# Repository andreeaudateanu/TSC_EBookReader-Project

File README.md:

# Proiect TSC - E-Book Reader
## Udățeanu Andreea-Laura

Acest proiect reprezinta un sistem embedded de tip **E-Book Reader**, bazat pe microcontrollerul **ESP32-C6**. Dispozitivul este capabil sa afiseze continut text pe un ecran **E-Paper**, oferind o solutie cu consum redus de energie, ideala pentru citirea offline a documentelor. Sistemul include, de asemenea, functionalitati precum citire de pe card SD, afisare dinamica, butoane pentru control si conectivitate extinsa prin interfata I2C.

# Diagrama bloc

# Functionalitati Hardware

Proiectul utilizeaza microcontrollerul **ESP32-C6-WROOM-1-N8**, un modul avansat cu suport pentru **Wi-Fi 6**, **Bluetooth Low Energy 5.0** si arhitectura **RISC-V**:

## Microcontrollerul ESP32-C6

- Modul avansat cu suport pentru **Wi-Fi 6**, **Bluetooth Low Energy 5.0** si arhitectura **RISC-V**
- **Interfete:** SPI, I2C, UART, USB, PWM, GPIO
	- **SPI (Serial Peripheral Interface):** este utilizat pentru comunicatia rapida cu dispozitive precum E-Paper Display-ul, memoria NOR Flash si cardul microSD.
	- **I2C (Inter-Integrated Circuit):** este o magistrala seriala bidirectionala cu doi pini (SDA si SCL), folosita pentru conectarea senzorului BME688, RTC-ului DS3231SN si monitorului de baterie MAX17048.
	- **UART (Universal Asynchronous Receiver/Transmitter):** interfata seriala folosita pentru comunicatie cu terminalul serial (TX/RX).
	- **GPIO (General Purpose Input/Output):** pini de uz general configurati ca intrare/iesire digitala – utilizati pentru butoane, controlul ecranului E-Ink, etc.

- **Caracteristici speciale:** ofera suport pentru moduri de economisire (deep sleep)
- **Conexiuni:** Interfata centrala – conecteaza toate modulele externe din cadrul proiectului(E-Paper, SD card, senzori, RTC, memorie NOR Flash, etc.)

## Alimentare si protectie

### MAX17048 – Monitorizare nivel de baterie Li-Po
- **Comunicare:** prin interfata I2C cu ESP32-C6 (SCL, SDA)
- **Iesire:** are la iesire un semnal ALERT pentru nivel critic baterie

### MCP73831 – Controller de incarcare a bateriei Li-Po
- **Incarcare:** utilizeaza o celula Li-Po prin USB (VBUS) → 4.2V
- **Curent de incarcare:** pana la 500 mA
- **LED-uri:** care indica starea de incarcare (CHG_LED)

### XC6220A331MR-G – Regulator de tensiune LDO
- Primeste la intrare 5V prin USB (VBUS), iar la iesire transmite o tensiune de 3.3V
- **Curent maxim:** 200 mA
- **Consum standby:** <1 µA

### Conector USB-C si Protectie ESD
- **Conector USB-C:** utilizat atat pentru alimentarea dispozitivului (VBUS) cat si pentru comunicatie USB cu microcontrollerul ESP32-C6.

- **Protectie ESD:** implementata pe liniile de date si alimentare folosind diode TVS dedicate:
USBLC6-2SC6Y – protejeaza liniile D+ si D−. PMF0501 – asigura protectie suplimentara pe linia de alimentare VBUS.
- **Utilizare:** permite incarcarea bateriei prin controllerul MCP73831, dar si programarea/diagnosticarea ESP32-C6 fara conexiuni suplimentare.

## Stocare

### SD Card
- **Functie:** citire/scriere a fisierelor E-Book din cardul microSD
- **Interfata:** SPI partajata cu E-Paper
- **Semnale:** SS_SD, MOSI, MISO, SCK
- **Slot:** 112A-TAAR-R03

### W25Q512JVEIQ – Memorie NOR Flash externa 64MB
- **Capacitate:** 64 MB
- **Interfata:** conectata la magistrala SPI (nu partajeaza cu E-Paper)
- **Semnale:** FLASH_CS, MOSI, MISO, SCK
- **Functie:** stocare fonturi, imagini, firmware, configurari

## Afisaj E-Paper

- Interfete SPI si GPIO dedicate, avand semnale precum: CS (EPD_CS), DC (EPD_DC), RST (EPD_RST), BUSY (EPD_BUSY), MOSI, SCK  
## **Header special EPD** cu 20 pini
## **Controlul alimentarii EPD:** 
Permite microcontrollerului sa activeze sau sa dezactiveze alimentarea modulului E-Paper pentru a economisi energie, avand la iesire o tensiune de 3V3
## **Selectare mod:** 
Comutator tip jumper pentru a selecta tipul de display (circuit EPD driver dedicat)
- Consum 0 in standby, ideal pentru afisaj static

## Senzor de Mediu BME688
- **Functionalitati:** temperatura, umiditate, presiune, calitate aer (VOC)
- **Interfata:** I2C
- **Pini:** SDA, SCL legati la magistrala I2C comuna
- **Tensiune de alimentare:** 3.3V

## Modul RTC – DS3231SN
- **Functie:** surprinde timpul real cu precizie ±2ppm, avand suport deep sleep
- **Conexiune:** I2C – partajeaza pinii SDA/SCL cu senzorul BME688 si cu monitorizatorul de baterie MAX17048
- **Iesiri:** semnal 32kHz si semnal de intrerupere (INT_RTC)
- **Alimentare:** 3.3V, avand si backup intern (capacitor)

## Functii de control, reset si protectie

### Butoane de Control
- **BOOT / RESET si IO/CHANGE personalizat:** conectate pe GPIO cu retele RC
- **Functii:** BOOT: initializare microcontroller in modul bootloader, RESET: resetare generala a sistemului si IO/CHANGE: buton suplimentare pentru interactiuni custom de tipul schimbarii paginii, a meniului, etc.

### BD5229G-TR – Voltage Supervisor
- **Rol:** detecteaza scaderile de tensiune (brown-out) sub un anumit prag critic si genereaza automat un semnal de rest
- **Asigura o pornirea sigura a sistemului

### Protectii ESD si Interfete Extensibile

- **Linii protejate:** toate magistralele sensibile – USB, SPI, I2C si GPIO – sunt protejate impotriva descarcarilor electrostatice (ESD) prin diode (ex: **USBLC6-2SC6Y**, **PGB1010603MR**, **MBR0530**).
- **Conector Qwiic / Stemma QT:** ofera o interfata I2C standard (3.3V, GND, SDA, SCL) pentru extinderea rapida a sistemului cu senzori si periferice de la SparkFun sau Adafruit, fara necesitatea lipirii.
- **Paduri de test:** sunt incluse pe PCB pentru depanare usoara, verificari de semnal si programare.

### Consum de energie estimativ

| Componenta                | Consum aproximativ   |
|:--------------------------|:---------------------|
| ESP32-C6                  | 120–150 mA           |
| E-Paper Display           | 20–40 mA             |
| Senzor BME688             | 1–2 mA               |
| RTC DS3231SN              | 200 µA               |
| SD Card                   | 40–100 mA            |
| MAX17048                  | 50 µA                |
| NOR Flash (W25Q512JVEIQ)  | 20 mA                |
| Total sistem - mod activ  | aprob. 300 mA        |
| Total sistem - deep sleep | max. 10 µA           |

Daca nu sunt dezactivate toate modulele fizic (cu MOSFET sau power gate), deep sleep-ul poate ajunge usor la 1–2 mA, deci <10 µA este ideal si atins doar cu management riguros al energiei.

### Alocarea pinilor

## E-Paper Display

| Pin ESP32-C6 | Functie     | Utilizare                               |
|--------------|-------------|------------------------------------------|
| IO3  (26)    | EPD_BUSY    | Semnalizează dacă ecranul este activ    |
| IO5  (5)     | EPD_DC      | Schimba modul intre date și comanda     |
| IO6  (6)     | SCK         | Linie de ceas SPI - transfer de date    |
| IO7  (7)     | MOSI        | Trimitere date către ecran prin SPI     |
| IO10 (11)    | EPD_CS      | Activare comunicație cu modulul EPD     |
| IO23 (21)    | EPD_RST     | Resetare ecran                          |
| IO20 (18)    | EPD_3V3_C   | Control tensiune de alimentare 3V3 EPD  |

## Magistrala I2C (MAX17048, RTC DS3231, BME688)

| Pin ESP32-C6 | Functie     | Utilizare                               |
|--------------|-------------|------------------------------------------|
| IO21 (19)    | SDA         | Linie de transmitere date I2C           |
| IO22 (20)    | SCL         | Linie de ceas I2C                       |
| IO19 (17)    | I2C_PW      | Pornire/oprire senzori I2C              |

## Modul RTC DS3231SN

| Pin ESP32-C6 | Functie     | Utilizare                               |
|--------------|-------------|------------------------------------------|
| IO0 (8)      | INT_RTC     | Semnal de întrerupere RTC               |
| IO1 (9)      | 32KHz       | Iesire ceas precis                      |
| IO18 (16)    | RTC_RST     | Resetare hardware al modulului RTC      |

## USB
| Pin ESP32-C6 | Functie     | Utilizare                               |
|--------------|-------------|------------------------------------------|
| IO12 (13)    | USB_D-      | Linia negativa de comunicatie USB       |
| IO13 (14)    | USB_D+      | Linia pozitiva de comunicatie USB       |

## Seriala UART

| Pin ESP32-C6 | Functie     | Utilizare                               |
|--------------|-------------|------------------------------------------|
| IO16 (25)    | TX          | Transmisie UART                         |
| IO17 (24)    | RX          | Receptie UART                           |

## SD Card

| Pin ESP32-C6 | Functie     | Utilizare                               |
|--------------|-------------|------------------------------------------|
| IO2 (27)     | MISO        | Receptie date                           |
| IO4 (4)      | SS_SD       | Selectare modul SD                      |
| IO6 (6)      | SCK         | Ceas SPI                                |
| IO7 (7)      | MOSI        | Transmisie date                         |

## Memorie Externa NOR Flash 64MB

| Pin ESP32-C6 | Functie     | Utilizare                               |
|--------------|-------------|------------------------------------------|
| IO11 (12)    | FLASH_CS    | Selectare chip NOR                      |
| IO2  (27)    | MISO        | Receptie date                           |
| IO6  (6)     | SCK         | Ceas SPI                                |
| IO7  (7)     | MOSI        | Transmisie date                         |

## Butoane

| Pin ESP32-C6 | Functie     | Utilizare                               |
|--------------|-------------|------------------------------------------|
| EN   (3)     | RESET       | Resetare microcontroller                |
| IO8  (10)    | IO/BOOT     | Buton BOOT (în modul de programare)     |
| IO15 (23)    | IO/CHANGE   | Buton custom pentru diverse actiuni     |

## Alimentare si Masă

| Pin ESP32-C6 | Functie     | Utilizare                               |
|--------------|-------------|------------------------------------------|
| Pin 2        | 3V3         | Alimentare principala la 3.3V           |
| Pin 1        | GND         | Conectare la masa                       |

## Bill of Materials

| Componenta | Link Cumpărare | Datasheet |
|------------|-----------------|-----------|
| Condensatoare Tantalum | [Buy](https://ro.mouser.com/ProductDetail/KYOCERA-AVX/TAJW107M010RNJ?qs=Wtp%252Bf%2FAeVqIH8v1VxV%252B1Rg%3D%3D) | [Datasheet](https://ro.mouser.com/datasheet/2/40/TAJ-3165264.pdf) |
| Rezistente R0402 | [Buy](https://store.comet.srl.ro/Search/?keywords=r0402#eyJpcHAiOiIyMCIsIm0iOiIiLCJrIjoicjA0MDIifQ%3D%3D) | [Datasheet](https://www.yageo.com/upload/media/product/products/datasheet/rchip/PYu-RC_Group_51_RoHS_L_12.pdf) |
| Condensatoare C0402 | [Buy](https://store.comet.srl.ro/CatalogueFarnell/Search/?keywords=c0402#eyJpcHAiOiIyMCIsImsiOiJjMDQwMiJ9) | [Datasheet](https://componentsearchengine.com/Datasheets/2/CC0402MRX5R5BB106.pdf) |
| 112A-TAAR-R03 | [Buy](https://store.comet.srl.ro/Catalogue/Product/43497/) | [Datasheet](https://www.snapeda.com/parts/112A-TAAR-R03/Attend/datasheet/) |
| SD0805S020S1R0 | [Buy](https://ro.mouser.com/ProductDetail/KYOCERA-AVX/SD0805S020S1R0?qs=jCA%252BPfw4LHbpkAoSnwrdjw%3D%3D) | [Datasheet](https://ro.mouser.com/datasheet/2/40/schottky-3165252.pdf) |
| MBR0530 | [Buy](https://ro.mouser.com/ProductDetail/onsemi-Fairchild/MBR0530?qs=VOMQJJE%252BBNniwJKcE3T43Q==) | [Datasheet](https://ro.mouser.com/datasheet/2/308/MBR0530_D-1810985.pdf) |
| CHG_LED | [Buy](https://ro.mouser.com/ProductDetail/Kingbright/KP-1608SURCK?qs=2JU0tDl2GZ3FuyEWfBV1%2Fg==) | [Datasheet](https://www.snapeda.com/parts/KP-1608SURCK/Kingbright/datasheet/) |
| USBLC6-2SC6Y | [Buy](https://ro.mouser.com/ProductDetail/STMicroelectronics/USBLC6-2SC6Y?qs=gNDSiZmRJS%2FOgDexvXkdow%3D%3D) | [Datasheet](https://ro.mouser.com/datasheet/2/389/usblc6_2sc6y-1852505.pdf) 
| PGB1010603MR | [Buy](https://www.digikey.com/en/products/detail/littelfuse-inc/PGB1010603MR/715755) | [Datasheet](https://www.littelfuse.com/assetdocs/pulseguard-esd-suppressors-pgb1-datasheet?assetguid=8a337998-d54d-466b-be4e-dc5bcd1f9321) |
| ESP32-C6-WROOM-1-N8 | [Buy](https://ro.mouser.com/ProductDetail/Espressif-Systems/ESP32-C6-WROOM-1-N8?qs=8Wlm6%252BaMh8ST02Gmwp74cw%3D%3D) | [Datasheet](https://ro.mouser.com/datasheet/2/891/Espressif_ESP32_C6_WROOM_1__Datasheet_V0_1_PRELIMI-3239987.pdf) |
| DS3231SN | [Buy](https://store.comet.srl.ro/Catalogue/Product/47690/) | [Datasheet](https://ro.mouser.com/datasheet/2/609/DS3231-3421123.pdf) |
| BME680 | [Buy](https://ro.mouser.com/ProductDetail/Bosch-Sensortec/BME688?qs=IS%252B4QmGtzzqQoVDscqwx3A%3D%3D) | [Datasheet](https://ro.mouser.com/datasheet/2/783/bst_bme688_fl000-2307034.pdf) |
| MAX17048 | [Buy](https://ro.mouser.com/ProductDetail/Analog-Devices-Maxim-Integrated/MAX17048G%2bT10?qs=D7PJwyCwLAoGnnn8jEPRBQ%3D%3D) | [Datasheet](https://ro.mouser.com/datasheet/2/609/MAX17048_MAX17049-3469099.pdf) |
| MCP73831 | [Buy](https://ro.mouser.com/ProductDetail/Microchip-Technology/MCP73831T-2ATI-OT?qs=yUQqVecv4qsZbioEUu%252B83g%3D%3D) | [Datasheet](https://ro.mouser.com/datasheet/2/268/MCP73831_Family_Data_Sheet_DS20001984H-3441711.pdf) |
| BD5229G-TR | [Buy](https://www.digikey.com/en/products/detail/rohm-semiconductor/BD5229G-TR/3663792) | [Datasheet](https://fscdn.rohm.com/en/products/databook/datasheet/ic/power/voltage_detector/bd52xxg-e.pdf) |
| W25Q512JVEIQ | [Buy](https://ro.mouser.com/ProductDetail/Winbond/W25Q512JVEIQ?qs=l7cgNqFNU1jw6svr3at6tA%3D%3D) | [Datasheet](https://ro.mouser.com/datasheet/2/949/Winbond_W25Q512JV_Datasheet-3240039.pdf) |
| XC6220A331MR-G | [Buy](https://ro.mouser.com/ProductDetail/Torex-Semiconductor/XC6220A331MR-G?qs=AsjdqWjXhJ8ZSWznL1J0gg%3D%3D) | [Datasheet](https://ro.mouser.com/datasheet/2/760/xc6220-3371556.pdf) |
| USB4110-GF-A | [Buy](https://ro.mouser.com/ProductDetail/GCT/USB4110-GF-A?qs=KUoIvG%2F9IlYiZvIXQjyJeA%3D%3D) | [Datasheet](https://ro.mouser.com/datasheet/2/837/GCT_USB4110_Product_Drawing___20k_cycles-3455479.pdf) |
| FH34SRJ | [Buy](https://ro.mouser.com/ProductDetail/Hirose-Connector/FH34SRJ-24S-0.5SH99?qs=vcbW%252B4%252BSTIpKBl5ap9J8Fw%3D%3D) | [Datasheet](https://ro.mouser.com/datasheet/2/185/FH34SRJ_24S_0_5SH_99__CL0580_1255_6_99_2DDrawing_0-1615044.pdf) |
| QWIIC_RIGHT_ANGLE | [Buy](https://ro.mouser.com/ProductDetail/SparkFun/PRT-14417?qs=wd5RIQLrsJhgdz%2FpmZ%2F3GQ==) | [Datasheet](https://ro.mouser.com/datasheet/2/813/Qwiic_Connector_Datasheet-1223982.pdf) |
| Bobine 744043680 | [Buy](https://ro.mouser.com/ProductDetail/Wurth-Elektronik/744043680?qs=PGXP4M47uW6VkZq%252BkzjrHA%3D%3D) | [Datasheet](https://www.we-online.com/components/products/datasheet/744043680.pdf) |
| Si1308EDL-T1-GE3 | [Buy](https://www.digikey.com/en/products/detail/vishay-siliconix/SI1308EDL-T1-GE3/4876435) | [Datasheet](https://www.vishay.com/docs/63399/si1308edl.pdf) |
| PFMF.050.1 | [Buy](https://ro.mouser.com/ProductDetail/EPCOS-TDK/B72520T0350K062?qs=dEfas%2FXlABIszF52uu7vrg%3D%3D) | [Datasheet](https://www.tdk-electronics.tdk.com/inf/75/db/CTVS_14/Surge_protection_series.pdf) |
| DMG2305UX-7 | [Buy](https://www.digikey.com/en/products/detail/diodes-incorporated/DMG2305UX-7/4340666) | [Datasheet](https://www.diodes.com/assets/Datasheets/DMG2305UX.pdf) |
| SJ (Solder Jumpers) | [Buy](https://grabcad.com/library/solder-jumpers-1) | [Datasheet](https://grabcad.com/library/solder-jumpers-1) |
| Butoane | [Buy](https://industry.panasonic.com/global/en/products/control/switch/light-touch/number/evqpuj02k) | [Datasheet](https://industry.panasonic.com/global/en/downloads?tab=catalog&small_g_cd=203&part_no=EVQPUJ02K) |
| CPH3225A | [Buy](https://www.digikey.com/en/products/detail/seiko-instruments/CPH3225A/8692444) | [Datasheet](https://mm.digikey.com/Volume0/opasdata/d220001/medias/docus/6537/rev05-CPHCPM.pdf) |

## Concluzii si observatii privind realizarea designului hardware
- In realizarea designului am urmarit respectarea regulilor impuse de ERC si DRC specifice. Amplasarea componentelor a fost facuta tinand cont atat de documentatiile tehnice oferite (dimensiuni si recomadari de plasare a componentelor), cat si de considerente legate de rutare si functionare optima a dispozitivului.
- Pentru evitarea erorilor in cadrul PCB-ului, am ajustat dimensiunile unor footprint-uri si am corectat pad-urile pentru a indeplini regulile de buna functionare. Am folosit regulile din checklist-ul de proiectare (inclusiv asezarea condensatorilor de decuplare plasati cat mai aproape de pinii VCC ai circuitelor integrate).
- Am distribuit traseele atat pe stratul top, cat si pe stratul bottom, incercand sa obtin cat mai putine vias-uri pe traseele de alimentare, pentru a reduce posibilitatea unei caderea de tensiune. Am rutat traseele de alimentare cu o latime de 0.3 mm, traseele de semnal avand latime de 0.15 mm conform cerintelor.
- Test pad-urile au fost amplasate cat mai eficient in zone relevante, la marginea placii: langa Header-ul E-Paper-ului si langa microcontroller.
- Am orientat antena modulului ESP32-C6 spre exteriorul placii, iar sub aceasta a fost lasata o zona decupata, conform recomandarilor pentru functionare optima a conexiunii wireless.
- Am pozitionat componentele cat mai bine pentru a putea fi integrate in carcasa proiectata, urmarind atat potrivirea mecanica, cat si o utilizare eficienta a spatiului disponibil. Am amplasat bateria in zona libera ramasa, astfel incat sa nu se intersecteze cu alte componente.
- Am tinut cont de amplasarea elementelor in functie de conectorul USB-C pentru asigurarea compatibilitatii cu carcasa. Butoanele au fost plasate cat mai eficient pentru a permite accesul la acestea si integrarea cu carcasa.
- In ansamblu, designul rezultat respecta cerintele functionale si mecanice, existand un echilibru intre robustete si eficienta.

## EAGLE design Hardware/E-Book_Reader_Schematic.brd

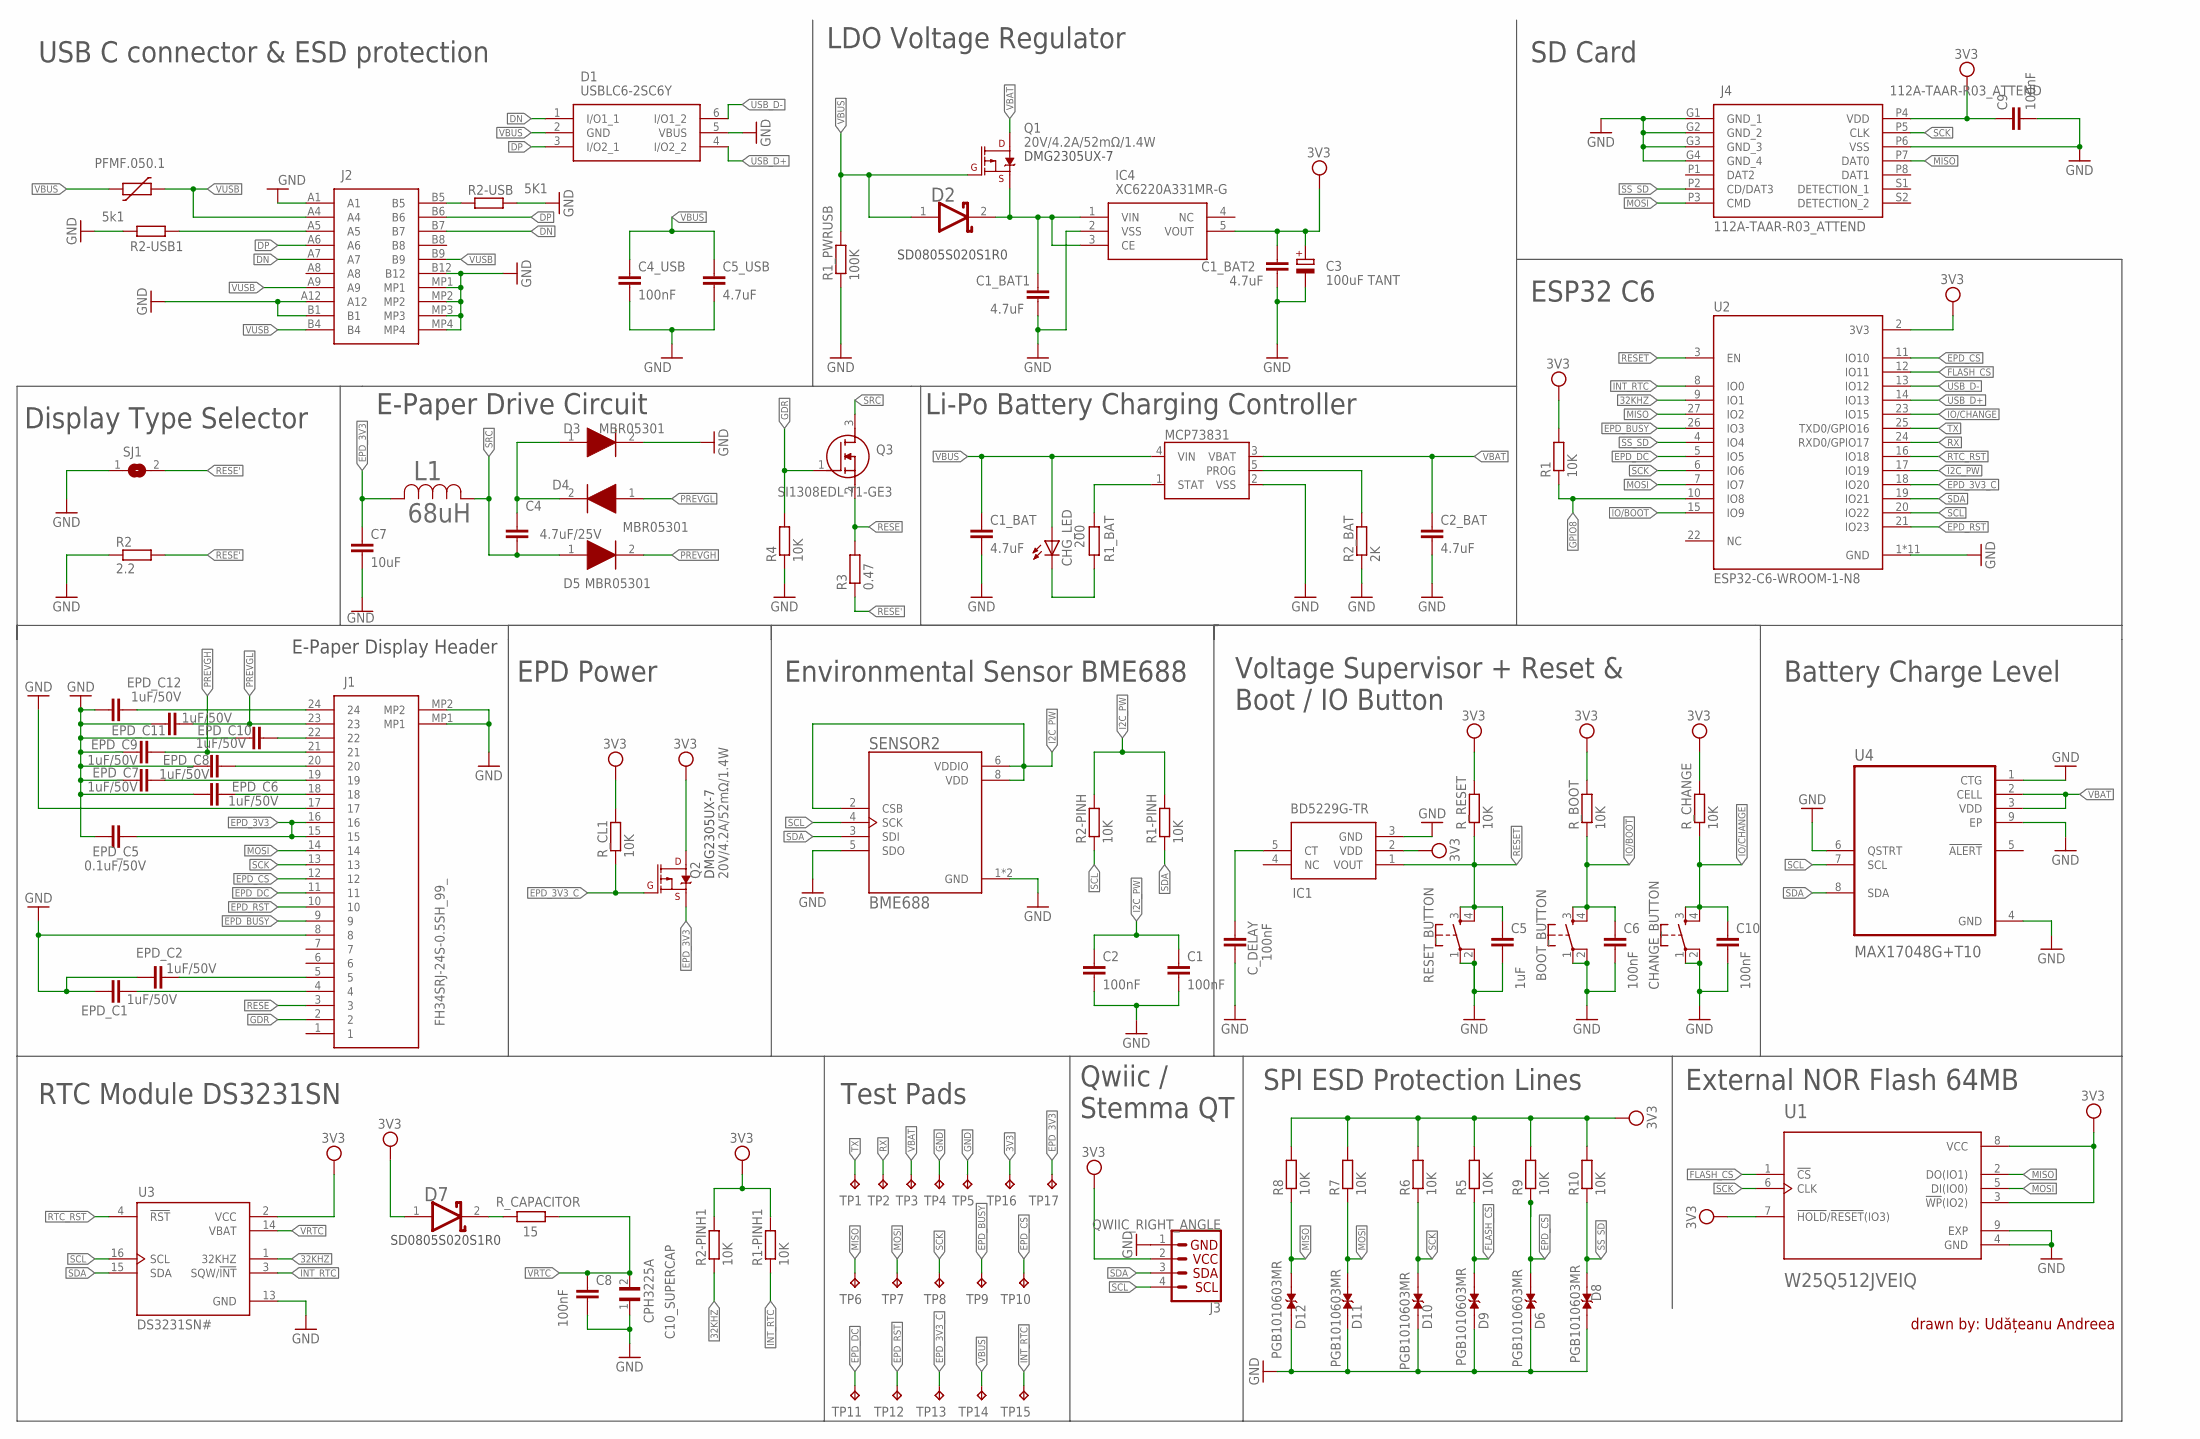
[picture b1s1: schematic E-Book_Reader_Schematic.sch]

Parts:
BOOT_BUTTON: BUTTON_CUSYOMV1; MYBUTTON
C1, C2, C6, C8, C10: 100nF; EAGLE-LTSPICE_C0402
C1_BAT, C1_BAT1, C1_BAT2, C2_BAT: 4.7uF; EAGLE-LTSPICE_C0402
C3: 100uF TANT; RCL_CT3528
C4: 4.7uF/25V; EAGLE-LTSPICE_C0402
C4_USB, C9: 100nF; ESP32_WROVER_EAGLE-LTSPICE_C0402
C5: 1uF; EAGLE-LTSPICE_C0402
C5_USB: 4.7uF; ESP32_WROVER_EAGLE-LTSPICE_C0402
C7: 10uF; EAGLE-LTSPICE_C0402
C10_SUPERCAP: CPH3225A; CAPCP3225X100N
CHANGE_BUTTON: BUTTON_CUSYOMV1; MYBUTTON
CHG_LED: ADAFRUIT_LEDCHIP-LED0603; ADAFRUIT_CHIP-LED0603
C_DELAY: 100nF; EAGLE-LTSPICE_C0402
D1: USBLC6-2SC6Y; SOT95P280X145-6N
D2, D7: SD0805S020S1R0; ESP32_WROVER_AVX---SD0805S020S1R0_AVX_SD0805S020S1R0_0
D3, D4, D5: MBR05301; SOD3716X135N
D6, D8, D9, D10, D11, D12: PGB1010603MR; DIOC1608X36N
EPD_C1, EPD_C2, EPD_C6, EPD_C7, EPD_C8, EPD_C9, EPD_C10, EPD_C11, EPD_C12: 1uF/50V; EAGLE-LTSPICE_C0402
EPD_C5: 0.1uF/50V; EAGLE-LTSPICE_C0402
IC1: BD5229G-TR; SOT95P280X125-5N
IC4: XC6220A331MR-G; SOT95P280X120-5N
J1: FH34SRJ-24S-0.5SH_99_; FH34SRJ24S05SH99
J2: SAMACSYS_PARTS_USB4110-GF-A; SAMACSYS_PARTS_USB4110GFA
J3: QWIIC_RIGHT_ANGLE; JST04_1MM_RA
J4: 112A-TAAR-R03_ATTEND; 112ATAARR03ATTEND
L1: 68uH; IND_4828-WE-TPC_WRE
MCP73831: ESP32_WROVER_SPARKFUN-IC-POWER_MCP73831; ESP32_WROVER_SPARKFUN-IC-POWER_SOT23-5
PFMF.050.1: ESP32C6_VARISTORCN1812; ESP32C6_VARISTOR_CT/CN1812
Q1, Q2: 20V/4.2A/52mΩ/1.4W; ESP32_WROVER_SPARKFUN-DISCRETESEMI_SOT23-3
Q3: SI1308EDL-T1-GE3; SOT65P210X110-3N
R1, R1-PINH, R1-PINH1, R2-PINH, R2-PINH1, R4, R5, R6, R7, R8, R9, R10: 10K; ESP32_WROVER_EAGLE-LTSPICE_R0402
R1_BAT: 200; ESP32_WROVER_EAGLE-LTSPICE_R0402
R1_PWRUSB: 100K; ESP32_WROVER_EAGLE-LTSPICE_R0402
R2: 2.2; ESP32_WROVER_EAGLE-LTSPICE_R0402
R2-USB: 5K1; ESP32_WROVER_EAGLE-LTSPICE_R0402
R2-USB1: 5k1; ESP32_WROVER_EAGLE-LTSPICE_R0402
R2_BAT: 2K; ESP32_WROVER_EAGLE-LTSPICE_R0402
R3: 0.47; ESP32_WROVER_EAGLE-LTSPICE_R0402
RESET_BUTTON: BUTTON_CUSYOMV1; MYBUTTON
R_BOOT: 10K; ESP32_WROVER_EAGLE-LTSPICE_R0402
R_CAPACITOR: 15; ESP32_WROVER_EAGLE-LTSPICE_R0402
R_CHANGE: 10K; ESP32_WROVER_EAGLE-LTSPICE_R0402
R_CL1: 10K; ESP32_WROVER_EAGLE-LTSPICE_R0402
R_RESET: 10K; ESP32_WROVER_EAGLE-LTSPICE_R0402
SENSOR2: BME688; ESP32_WROVER_BME680_PSON80P300X300X100-8N
SJ1: SJ
TP1: TPTP20R; TP20R
TP2, TP3, TP4, TP5, TP6, TP7, TP8, TP9, TP10, TP11, TP12, TP13, TP14, TP15, TP16, TP17: TP; TP20R
U1: W25Q512JVEIQ; SON127P600X800X80-9N
U2: ESP32-C6-WROOM-1-N8; XCVR_ESP32-C6-WROOM-1-N8
U3: DS3231SN#; SOIC127P1032X265-16N
U4: MAX17048G+T10; SON50P200X200X80-9N

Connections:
3V3: C1_BAT2.1, C3.+, C9.1, D7.1 (ANODE), IC1.2 (VDD), IC4.5 (VOUT), J3.2, J4.P4 (VDD), Q2.3 (D), R1.2, R1-PINH1.2, R2-PINH1.2, R5.2, R6.2, R7.2, R8.2, R9.2, R10.2, R_BOOT.2, R_CHANGE.2, R_CL1.2, R_RESET.2, TP16.TP, U1.3 (!WP!(IO2)), U1.7 (!HOLD!/!RESET!(IO3)), U1.8 (VCC), U2.2 (3V3), U3.2 (VCC)
32KHZ: R2-PINH1.1, U2.9 (IO1), U3.1 (32KHZ)
DN: D1.1 (I/O1_1), J2.A7, J2.B7
DP: D1.3 (I/O2_1), J2.A6, J2.B6
EPD_3V3: C7.1, EPD_C5.1, J1.15, J1.16, L1.2, Q2.2 (S), TP17.TP
EPD_3V3_C: Q2.1 (G), R_CL1.1, TP13.TP, U2.18 (IO20)
EPD_BUSY: J1.9, TP9.TP, U2.26 (IO3)
EPD_CS: D6.2, J1.12, R9.1, TP10.TP, U2.11 (IO10)
EPD_DC: J1.11, TP11.TP, U2.5 (IO5)
EPD_RST: J1.10, TP12.TP, U2.21 (IO23)
FLASH_CS: D9.2, R5.1, U1.1 (!CS), U2.12 (IO11)
GDR: J1.2, Q3.1 (G), R4.2
GND: BOOT_BUTTON.1, BOOT_BUTTON.2, C1.2, C1_BAT.2, C1_BAT1.2, C1_BAT2.2, C2.2, C2_BAT.2, C3.-, C4_USB.2, C5.2, C5_USB.2, C6.2, C7.2, C8.2, C9.2, C10.2, C10_SUPERCAP.1, CHANGE_BUTTON.1, CHANGE_BUTTON.2, C_DELAY.2, D1.5 (VBUS), D3.2 (K), D6.1, D8.1, D9.1, D10.1, D11.1, D12.1, EPD_C1.2, EPD_C2.2, EPD_C5.2, EPD_C6.2, EPD_C7.2, EPD_C8.2, EPD_C9.2, EPD_C10.2, EPD_C11.2, EPD_C12.2, IC1.3 (GND), IC4.2 (VSS), J1.8, J1.17, J1.MP1, J1.MP2, J2.A1, J2.A12, J2.B1, J2.B12, J2.MP1, J2.MP2, J2.MP3, J2.MP4, J3.1, J4.G1 (GND_1), J4.G2 (GND_2), J4.G3 (GND_3), J4.G4 (GND_4), J4.P6 (VSS), MCP73831.2 (VSS), R1_PWRUSB.1, R2.1, R2-USB.2, R2-USB1.1, R2_BAT.1, R4.1, RESET_BUTTON.1, RESET_BUTTON.2, SENSOR2.1 (GND), SENSOR2.5 (SDO), SENSOR2.7 (GND), SJ1.1, TP4.TP, TP5.TP, U1.4 (GND), U1.9 (EXP), U2.1 (GND), U2.28 (GND), U2.29_1 (GND), U2.29_2 (GND), U2.29_3 (GND), U2.29_4 (GND), U2.29_5 (GND), U2.29_6 (GND), U2.29_7 (GND), U2.29_8 (GND), U2.29_9 (GND), U3.13 (GND), U4.1 (CTG), U4.4 (GND), U4.6 (QSTRT), U4.9 (EP)
GPIO8: R1.1, U2.10 (IO8)
I2C_PW: C1.1, C2.1, R1-PINH.2, R2-PINH.2, SENSOR2.2 (CSB), SENSOR2.6 (VDDIO), SENSOR2.8 (VDD), U2.17 (IO19)
INT_RTC: R1-PINH1.1, TP15.TP, U2.8 (IO0), U3.3 (SQW/!INT)
IO/BOOT: BOOT_BUTTON.3, BOOT_BUTTON.4, C6.1, R_BOOT.1, U2.15 (IO9)
IO/CHANGE: C10.1, CHANGE_BUTTON.3, CHANGE_BUTTON.4, R_CHANGE.1, U2.23 (IO15)
MISO: D12.2, J4.P7 (DAT0), R8.1, TP6.TP, U1.2 (DO(IO1)), U2.27 (IO2)
MOSI: D11.2, J1.14, J4.P3 (CMD), R7.1, TP7.TP, U1.5 (DI(IO0)), U2.7 (IO7)
unnamed: MCP73831.1 (STAT), R1_BAT.2
unnamed: J2.A5, R2-USB1.2
unnamed: C1_BAT1.1, D2.2 (CATHODE), IC4.1 (VIN), IC4.3 (CE), Q1.2 (S)
unnamed: J2.B5, R2-USB.1
unnamed: CHG_LED.C, R1_BAT.1
unnamed: C4.1, D3.1 (A), D4.2 (K)
unnamed: EPD_C12.1, J1.24
unnamed: MCP73831.5 (PROG), R2_BAT.2
unnamed: C_DELAY.1, IC1.5 (CT)
unnamed: EPD_C10.1, J1.22
unnamed: D7.2 (CATHODE), R_CAPACITOR.2
unnamed: EPD_C8.1, J1.20
unnamed: EPD_C7.1, J1.19
unnamed: EPD_C6.1, J1.18
unnamed: EPD_C1.1, J1.4
unnamed: EPD_C2.1, J1.5
PREVGH: D5.2 (K), EPD_C9.1, J1.21
PREVGL: D4.1 (A), EPD_C11.1, J1.23
RESE: J1.3, Q3.2 (S), R3.2
RESE': R2.2, R3.1, SJ1.2
RESET: C5.1, IC1.1 (VOUT), RESET_BUTTON.3, RESET_BUTTON.4, R_RESET.1, U2.3 (EN)
RTC_RST: U2.16 (IO18), U3.4 (!RST)
RX: TP2.TP, U2.24 (RXD0/GPIO17)
SCK: D10.2, J1.13, J4.P5 (CLK), R6.1, TP8.TP, U1.6 (CLK), U2.6 (IO6)
SCL: J3.4, R2-PINH.1, SENSOR2.4 (SCK), U2.20 (IO22), U3.16 (SCL), U4.7 (SCL)
SDA: J3.3, R1-PINH.1, SENSOR2.3 (SDI), U2.19 (IO21), U3.15 (SDA), U4.8 (SDA)
SRC: C4.2, D5.1 (A), L1.1, Q3.3 (D)
SS_SD: D8.2, J4.P2 (CD/DAT3), R10.1, U2.4 (IO4)
TX: TP1.TP, U2.25 (TXD0/GPIO16)
USB_D+: D1.4 (I/O2_2), U2.14 (IO13)
USB_D-: D1.6 (I/O1_2), U2.13 (IO12)
VBAT: C2_BAT.1, MCP73831.3 (VBAT), Q1.3 (D), TP3.TP, U4.2 (CELL), U4.3 (VDD)
VBUS: C1_BAT.1, C4_USB.1, C5_USB.1, CHG_LED.A, D1.2 (GND), D2.1 (ANODE), MCP73831.4 (VIN), PFMF.050.1.1, Q1.1 (G), R1_PWRUSB.2, TP14.TP
VRTC: C8.1, C10_SUPERCAP.2, R_CAPACITOR.1, U3.14 (VBAT)
VUSB: J2.A4, J2.A9, J2.B4, J2.B9, PFMF.050.1.2

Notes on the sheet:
USB C connector & ESD protection
LDO Voltage Regulator
SD Card
ESP32 C6
Li-Po Battery Charging Controller
E-Paper Drive Circuit
Display Type Selector
E-Paper Display Header
EPD Power
Environmental Sensor BME688
Voltage Supervisor + Reset & Boot / IO Button
Battery Charge Level
External NOR Flash 64MB
SPI ESD Protection Lines
Qwiic / Stemma QT
Test Pads
RTC Module DS3231SN
SD0805S020S1R0
DMG2305UX-7
drawn by: Udățeanu Andreea
112A-TAAR-R03_ATTEND

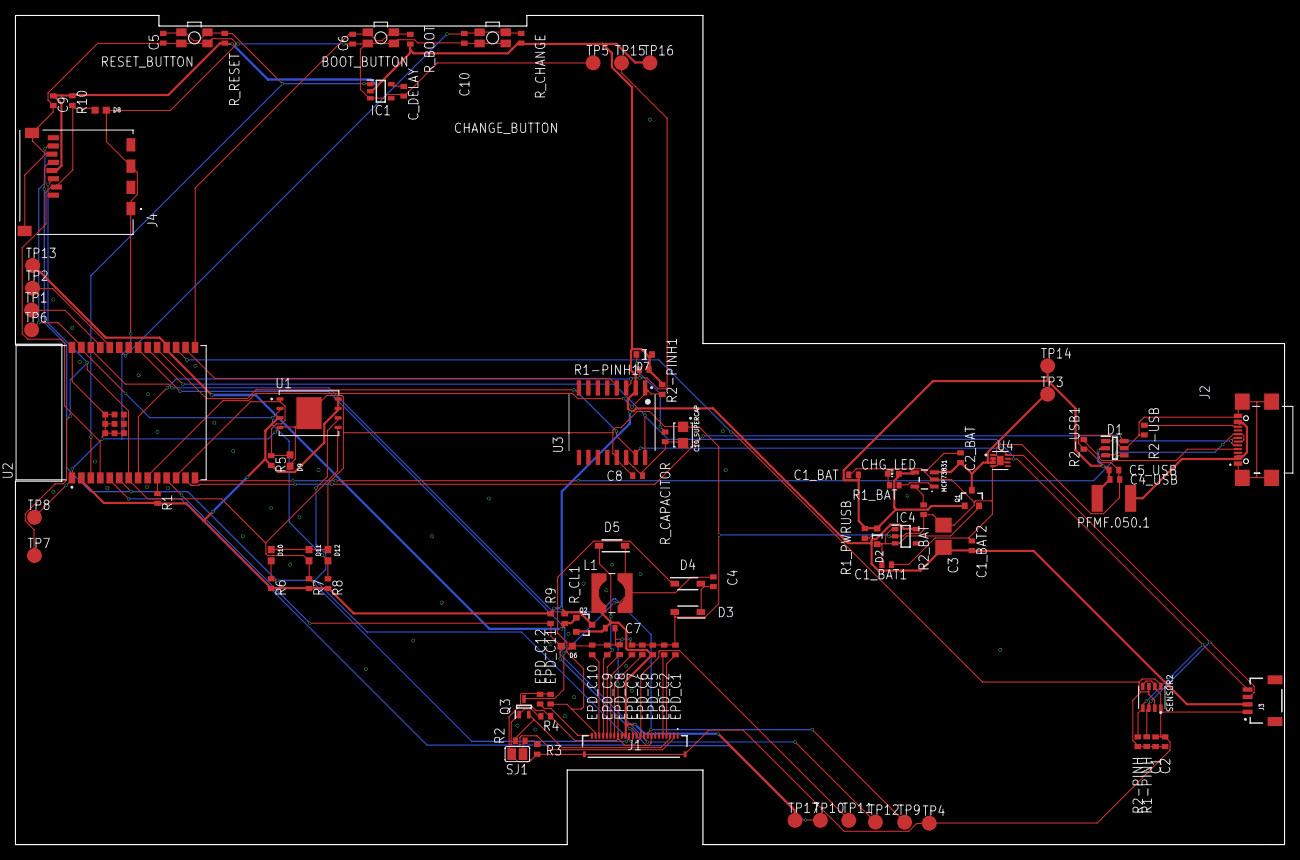
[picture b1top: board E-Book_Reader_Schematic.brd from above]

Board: 2 copper layers, 170.2 x 111.2 mm, 103 parts (0 on the bottom side), 55 nets.

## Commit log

2025-04-06 Create LICENSE
2025-04-06 Schematic Files Uploaded
2025-04-06 Renders of E-Book Reader Uploaded
2025-04-06 3D Model Uploaded
2025-04-06 Expanded 3D PCB .step file Uploaded
2025-04-13 Schematic Modified Fixes #5 Fixes #6 Fixes #7
2025-04-13 PCB Modified Fixes #1 Fixes #2 Fixes #3 Fixes #4
2025-04-13 3D Model Modified Fixes #8 Fixes #9 Fixes #10

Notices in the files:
parts and their libraries:
COPYRIGHT: Copyright (C) 2024 Ultra Librarian. All rights reserved.
